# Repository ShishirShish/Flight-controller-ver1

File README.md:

🛩️ Flight Controller – Custom STM32-Based Design
This repository contains the complete hardware design of a custom STM32-based flight controller, intended for multirotor UAVs and embedded control applications.
The project focuses on robust power design, precise sensor integration, and clean signal routing, suitable for research, academic, and prototyping use.

📌 Features Overview
Microcontroller: STM32F446RETx
Sensors:
6-axis IMU (Accelerometer + Gyroscope)
Barometric pressure sensor
Clocking: External 8 MHz crystal
Power:
USB-powered input
Onboard 3.3 V LDO regulation
Proper filtering and decoupling

Interfaces:

USB (device)
I²C
SPI
UART
CAN

SWD (programming & debugging)

Motor Control:
PWM outputs for ESCs

Timer-based channels

Designed in: KiCad 9.0.6

🧠 Hardware Architecture
1️⃣ Main Controller

STM32F446RE

External 8 MHz crystal with 20 pF load capacitors

SWD interface for debugging and flashing

Proper VCAP, VDDA, and decoupling network

2️⃣ Sensors
IMU (Accelerometer + Gyro)

I²C interface

Dedicated local decoupling capacitors

Pull-up resistors on SDA/SCL

Interrupt pins routed to MCU

Barometer

I²C interface

Configurable I²C address

Separate power filtering

3️⃣ Power Supply

USB 5 V input

Fuse and reverse protection

Low-noise 3.3 V LDO regulator

Power indication LED

Proper bulk and ceramic capacitors

4️⃣ ESC & PWM Outputs

Timer-based PWM outputs

Dedicated headers for ESC signal + power

Designed to support multirotor configurations

5️⃣ Communication Interfaces

USB (DFU / CDC capable)

Multiple UARTs

SPI (sensor expansion)

CAN bus

GPIO expansion headers

🔌 Pin Highlights
Interface	Purpose
TIM2 / TIM3	PWM outputs for ESCs
I2C1 / I2C3	IMU & Barometer
USB FS	Programming / telemetry
SWD	Debugging
CAN	External communication
ADC	Voltage / analog sensing
🧪 Design Considerations

Extensive decoupling and filtering

Ferrite bead isolation for analog supply

RC low-pass filters for ADC inputs

Separate sensor and digital domains

Designed with noise-sensitive IMU placement in mind

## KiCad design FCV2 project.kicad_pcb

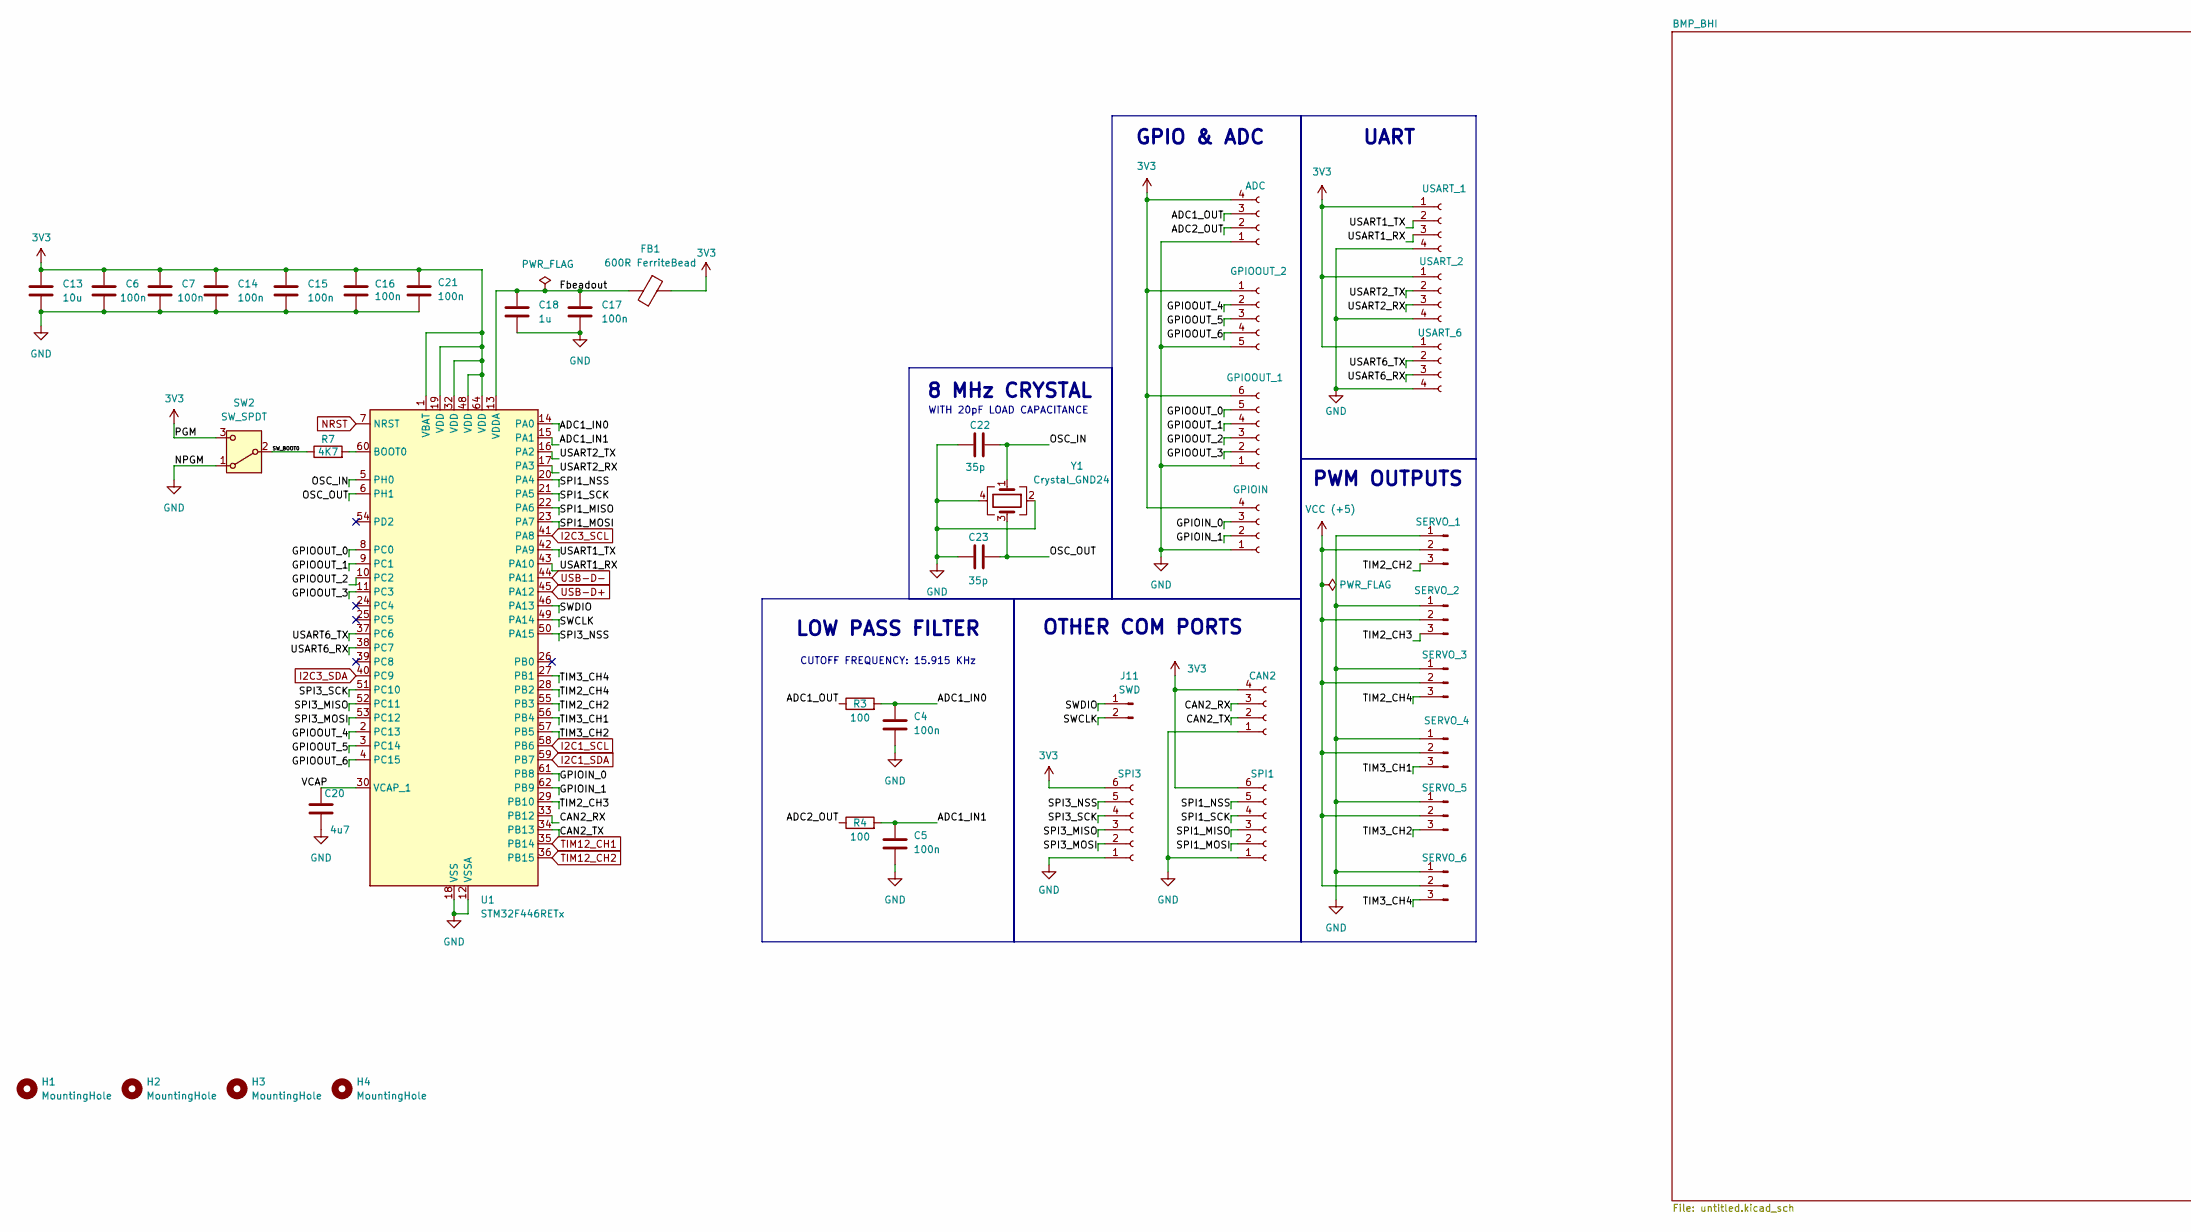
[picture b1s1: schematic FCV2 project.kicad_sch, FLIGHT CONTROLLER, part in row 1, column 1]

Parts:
C4, C5, C6, C7, C14, C15, C16, C17, C21: 100n; C_0402_1005Metric
C13: 10u; C_0603_1608Metric
C18: 1u; C_0402_1005Metric
C20: 4u7; C_0603_1608Metric
C22, C23: 35p; C_0402_1005Metric
FB1: 600R FerriteBead; L_0603_1608Metric
H1, H2, H3, H4: MountingHole; MountingHole_2.2mm_M2
J1: SPI3; PinSocket_1x06_P2.54mm_Vertical
J2: GPIOOUT_1; PinSocket_1x06_P2.54mm_Vertical
J3: USART_1; PinSocket_1x04_P2.54mm_Vertical
J4: GPIOIN; PinSocket_1x04_P2.54mm_Vertical
J5: ADC; PinSocket_1x04_P2.54mm_Vertical
J6: USART_2; PinSocket_1x04_P2.54mm_Vertical
J7: USART_6; PinSocket_1x04_P2.54mm_Vertical
J8: SERVO_1; PinHeader_1x03_P2.54mm_Vertical
J9: SERVO_2; PinHeader_1x03_P2.54mm_Vertical
J10: GPIOOUT_2; PinSocket_1x05_P2.54mm_Vertical
J11: SWD; PinSocket_1x02_P2.54mm_Vertical
J12: SERVO_5; PinHeader_1x03_P2.54mm_Vertical
J13: SERVO_4; PinHeader_1x03_P2.54mm_Vertical
J14: SERVO_6; PinHeader_1x03_P2.54mm_Vertical
J15: SERVO_3; PinHeader_1x03_P2.54mm_Vertical
J17: SPI1; PinSocket_1x06_P2.54mm_Vertical
J18: CAN2; PinSocket_1x04_P2.54mm_Vertical
R3, R4: 100; R_0402_1005Metric
R7: 4K7; R_0402_1005Metric
SW2: SW_SPDT; SW_SPDT_PCM12
U1: STM32F446RETx; LQFP-64_10x10mm_P0.5mm
Y1: Crystal_GND24; Crystal_SMD_3225-4Pin_3.2x2.5mm

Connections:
3V3: C6.1, C7.1, C13.1, C14.1, C15.1, C16.1, C21.2, FB1.1, J1.6, J2.6, J3.1, J4.4, J5.4, J6.1, J7.1, J10.1, J17.6, J18.4, SW2.3 (C), U1.1 (VBAT), U1.19 (VDD), U1.32 (VDD), U1.48 (VDD), U1.64 (VDD); also elsewhere on the board
/ADC1_IN0: C4.2, R3.2, U1.14 (PA0)
/ADC1_IN1: C5.2, R4.2, U1.15 (PA1)
/ADC1_OUT: J5.3, R3.1
/ADC2_OUT: J5.2, R4.1
/CAN2_RX: J18.3, U1.33 (PB12)
/CAN2_TX: J18.2, U1.34 (PB13)
/Fbeadout: C17.1, C18.1, FB1.2, U1.13 (VDDA)
/GPIOIN_0: J4.3, U1.61 (PB8)
/GPIOIN_1: J4.2, U1.62 (PB9)
/GPIOOUT_0: J2.5, U1.8 (PC0)
/GPIOOUT_1: J2.4, U1.9 (PC1)
/GPIOOUT_2: J2.3, U1.10 (PC2)
/GPIOOUT_3: J2.2, U1.11 (PC3)
/GPIOOUT_4: J10.2, U1.2 (PC13)
/GPIOOUT_5: J10.3, U1.3 (PC14)
/GPIOOUT_6: J10.4, U1.4 (PC15)
/OSC_IN: C22.1, U1.5 (PH0), Y1.1
/OSC_OUT: C23.1, U1.6 (PH1), Y1.3
/SPI1_MISO: J17.3, U1.22 (PA6)
/SPI1_MOSI: J17.2, U1.23 (PA7)
/SPI1_NSS: J17.5, U1.20 (PA4)
/SPI1_SCK: J17.4, U1.21 (PA5)
/SPI3_MISO: J1.3, U1.52 (PC11)
/SPI3_MOSI: J1.2, U1.53 (PC12)
/SPI3_NSS: J1.5, U1.50 (PA15)
/SPI3_SCK: J1.4, U1.51 (PC10)
/SWCLK: J11.2, U1.49 (PA14)
/SWDIO: J11.1, U1.46 (PA13)
/SW_BOOT0: R7.1, SW2.2 (B)
/TIM2_CH2: J8.3, U1.55 (PB3)
/TIM2_CH3: J9.3, U1.29 (PB10)
/TIM2_CH4: J15.3, U1.28 (PB2)
/TIM3_CH1: J13.3, U1.56 (PB4)
/TIM3_CH2: J12.3, U1.57 (PB5)
/TIM3_CH4: J14.3, U1.27 (PB1)
/USART1_RX: J3.3, U1.43 (PA10)
/USART1_TX: J3.2, U1.42 (PA9)
/USART2_RX: J6.3, U1.17 (PA3)
/USART2_TX: J6.2, U1.16 (PA2)
/USART6_RX: J7.3, U1.38 (PC7)
/USART6_TX: J7.2, U1.37 (PC6)
/VCAP: C20.1, U1.30 (VCAP_1)
GND: C4.1, C5.1, C6.2, C7.2, C13.2, C14.2, C15.2, C16.2, C17.2, C18.2, C20.2, C21.1, C22.2, C23.2, J1.1, J2.1, J3.4, J4.1, J5.1, J6.4, J7.4, J8.1, J9.1, J10.5, J12.1, J13.1, J14.1, J15.1, J17.1, J18.1, SW2.1 (A), U1.12 (VSSA), U1.18 (VSS), U1.31 (VSS), U1.47 (VSS), U1.63 (VSS), Y1.2, Y1.4; also elsewhere on the board
I2C1_SCL: U1.58 (PB6); also elsewhere on the board
I2C1_SDA: U1.59 (PB7); also elsewhere on the board
I2C3_SCL: U1.41 (PA8); also elsewhere on the board
I2C3_SDA: U1.40 (PC9); also elsewhere on the board
NRST: U1.7 (NRST); also elsewhere on the board
unnamed: R7.2, U1.60 (BOOT0)
TIM12_CH1: U1.35 (PB14); also elsewhere on the board
TIM12_CH2: U1.36 (PB15); also elsewhere on the board
USB-D+: U1.45 (PA12); also elsewhere on the board
USB-D-: U1.44 (PA11); also elsewhere on the board
VCC (+5): J8.2, J9.2, J12.2, J13.2, J14.2, J15.2; also elsewhere on the board

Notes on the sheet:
GPIO & ADC
CUTOFF FREQUENCY: 15.915 KHz
LOW PASS FILTER
UART
PWM OUTPUTS
OTHER COM PORTS
8 MHz CRYSTAL
WITH 20pF LOAD CAPACITANCE

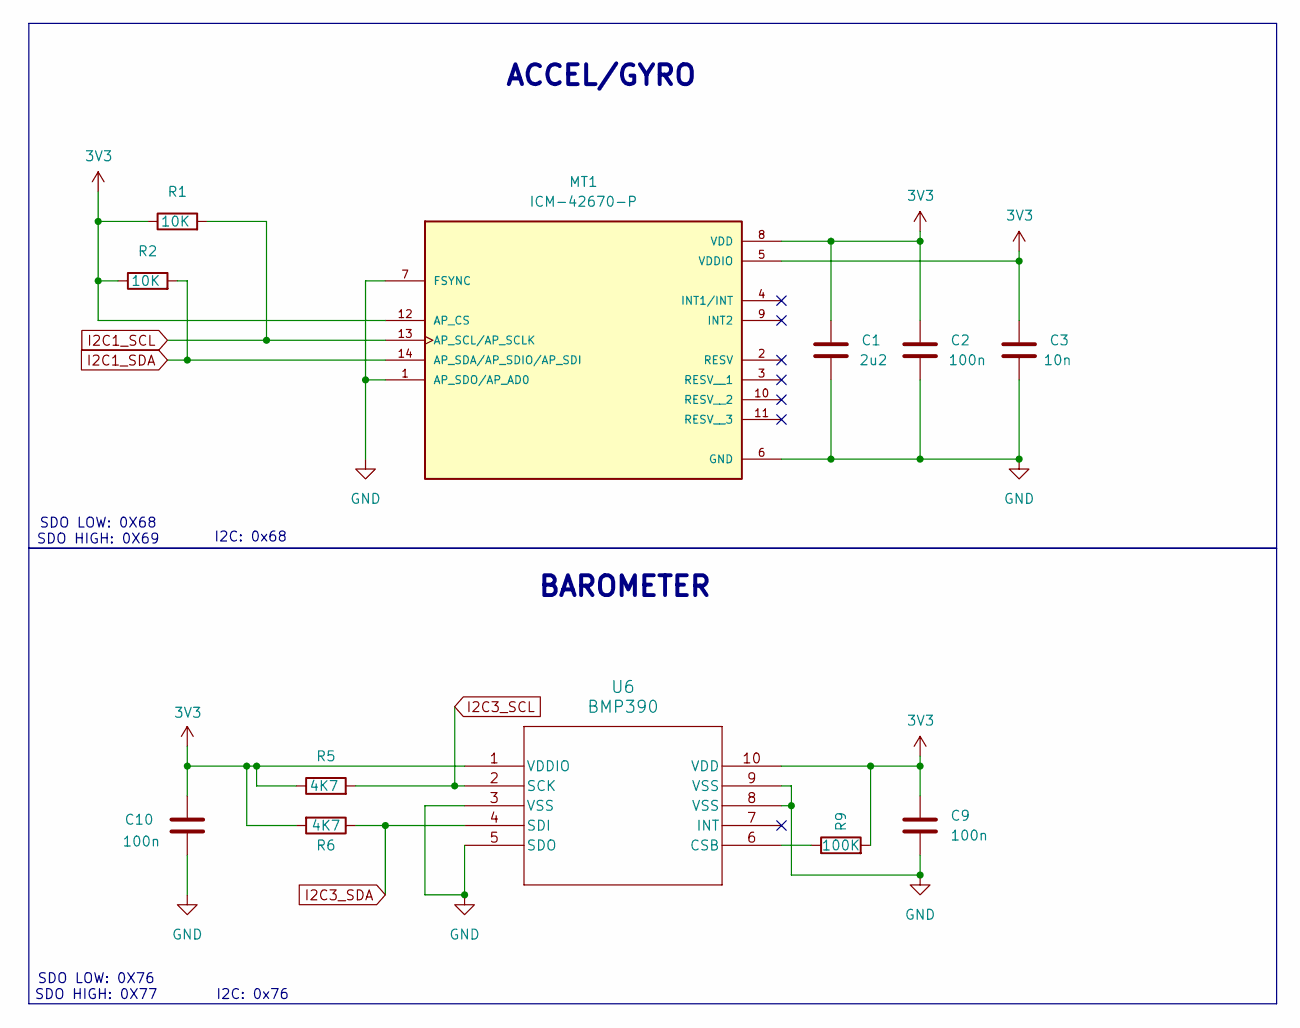
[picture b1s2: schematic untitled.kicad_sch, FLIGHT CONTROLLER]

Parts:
C1: 2u2; C_0603_1608Metric
C2, C9, C10: 100n; C_0402_1005Metric
C3: 10n; C_0402_1005Metric
MT1: ICM-42670-P; LGA14_2.5X3X0.76_IVS; PARTREV 1.1
R1, R2: 10K; R_0402_1005Metric
R5, R6: 4K7; R_0402_1005Metric
R9: 100K; R_0402_1005Metric
U6: BMP390

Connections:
3V3: C1.1, C2.1, C3.1, C9.1, C10.1, MT1.5 (VDDIO), MT1.8 (VDD), MT1.12 (AP_CS), R1.1, R2.1, R5.1, R6.2, R9.2, U6.1 (VDDIO), U6.10 (VDD); also elsewhere on the board
GND: C1.2, C2.2, C3.2, C9.2, C10.2, MT1.1 (AP_SDO/AP_AD0), MT1.6 (GND), MT1.7 (FSYNC), U6.3 (VSS), U6.5 (SDO), U6.8 (VSS), U6.9 (VSS); also elsewhere on the board
I2C1_SCL: MT1.13 (AP_SCL/AP_SCLK), R1.2; also elsewhere on the board
I2C1_SDA: MT1.14 (AP_SDA/AP_SDIO/AP_SDI), R2.2; also elsewhere on the board
I2C3_SCL: R5.2, U6.2 (SCK); also elsewhere on the board
I2C3_SDA: R6.1, U6.4 (SDI); also elsewhere on the board
unnamed: R9.1, U6.6 (CSB)

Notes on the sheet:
I2C: 0x76
ACCEL/GYRO
SDO LOW: 0X68 SDO HIGH: 0X69
BAROMETER
SDO LOW: 0X76 SDO HIGH: 0X77
I2C: 0x68

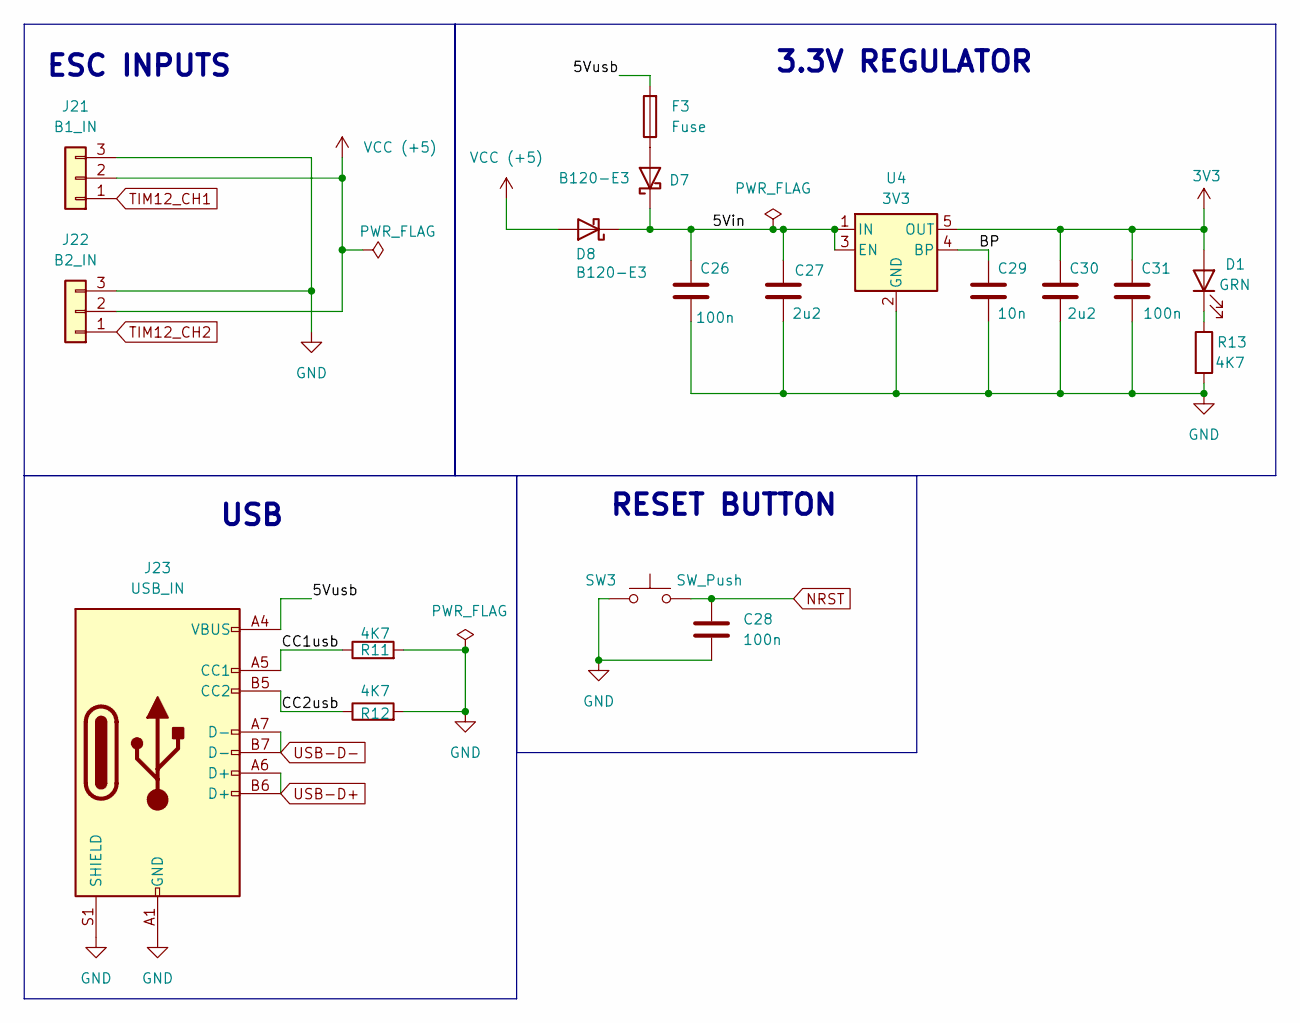
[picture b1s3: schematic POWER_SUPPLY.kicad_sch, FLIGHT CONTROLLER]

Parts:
C26, C28, C31: 100n; C_0402_1005Metric
C27, C30: 2u2; C_0603_1608Metric
C29: 10n; C_0402_1005Metric
D1: GRN; LED_0603_1608Metric
D7, D8: B120-E3; D_0603_1608Metric
F3: Fuse; Fuse_1206_3216Metric
J21: B1_IN; PinHeader_1x03_P2.54mm_Vertical
J22: B2_IN; PinHeader_1x03_P2.54mm_Vertical
J23: USB_IN; USB_C_Receptacle_GCT_USB4105-xx-A_16P_TopMnt_Horizontal
R11, R12, R13: 4K7; R_0402_1005Metric
SW3: SW_Push; SW_Push_1P1T_NO_6x6mm_H9.5mm
U4: 3V3; SOT-23-5

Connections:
3V3: C30.1, C31.1, D1.2 (A), U4.5 (OUT); also elsewhere on the board
/POWER SUPPLY/5Vin: C26.1, C27.1, D7.1 (K), D8.1 (K), U4.1 (IN), U4.3 (EN)
/POWER SUPPLY/5Vusb: F3.2, J23.A4 (VBUS), J23.A9 (VBUS), J23.B4 (VBUS), J23.B9 (VBUS)
/POWER SUPPLY/BP: C29.1, U4.4 (BP)
/POWER SUPPLY/CC1usb: J23.A5 (CC1), R11.1
/POWER SUPPLY/CC2usb: J23.B5 (CC2), R12.1
GND: C26.2, C27.2, C28.2, C29.2, C30.2, C31.2, J21.3, J22.3, J23.A1 (GND), J23.A12 (GND), J23.B1 (GND), J23.B12 (GND), J23.S1 (SHIELD), R11.2, R12.2, R13.2, SW3.1, U4.2 (GND); also elsewhere on the board
NRST: C28.1, SW3.2; also elsewhere on the board
unnamed: D1.1 (K), R13.1
unnamed: D7.2 (A), F3.1
TIM12_CH1: J21.1; also elsewhere on the board
TIM12_CH2: J22.1; also elsewhere on the board
USB-D+: J23.A6 (D+), J23.B6 (D+); also elsewhere on the board
USB-D-: J23.A7 (D-), J23.B7 (D-); also elsewhere on the board
VCC (+5): D8.2 (A), J21.2, J22.2; also elsewhere on the board

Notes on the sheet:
USB
RESET BUTTON
ESC INPUTS
3.3V REGULATOR

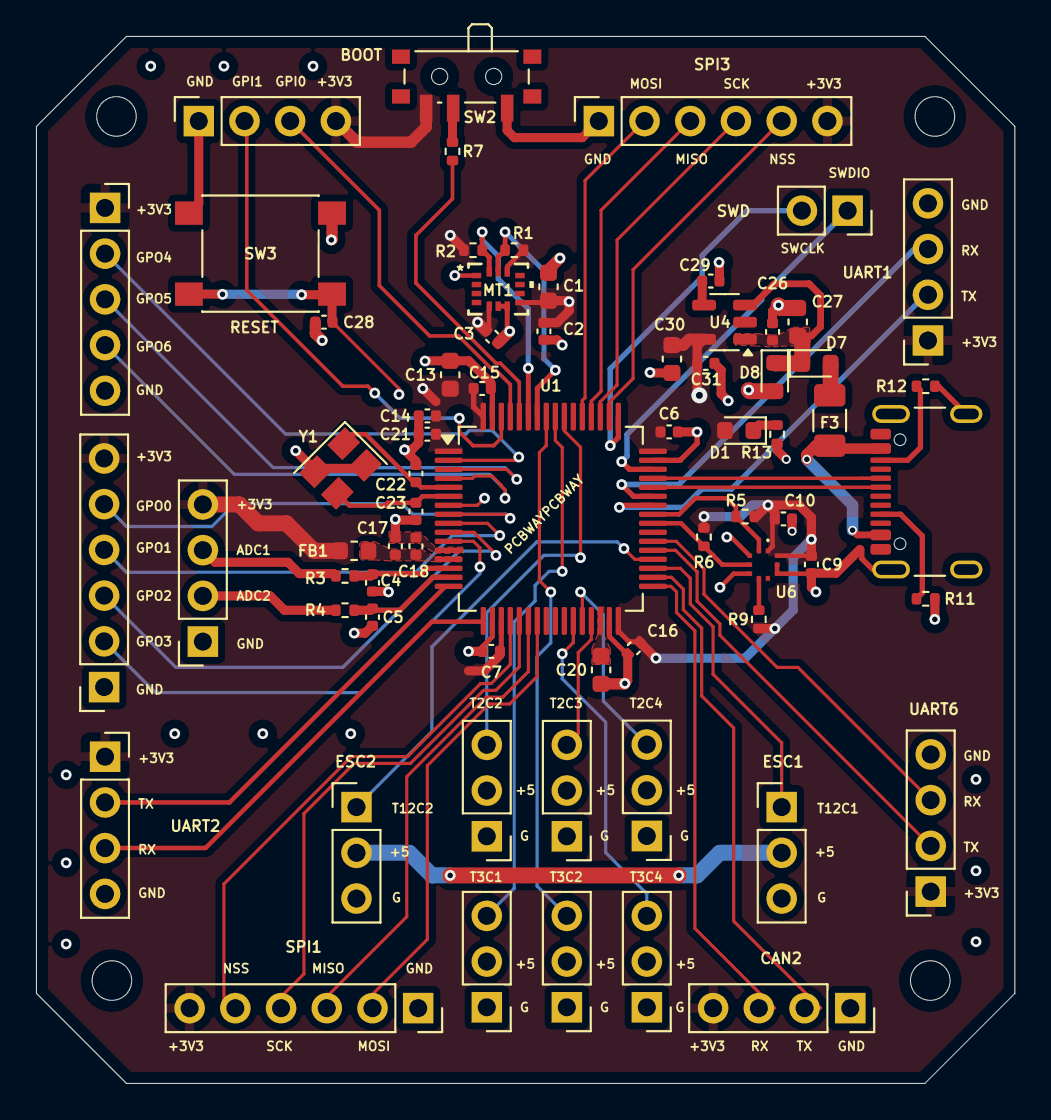
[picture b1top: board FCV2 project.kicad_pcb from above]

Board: 4 copper layers, 54.4 x 58.2 mm, 72 parts (0 on the bottom side), 63 nets.

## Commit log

2026-02-09 Add README for STM32-based flight controller project
    This README provides an overview of the STM32-based flight controller, detailing its features, hardware architecture, and design considerations.
2026-02-10 Create Custom Firmware
